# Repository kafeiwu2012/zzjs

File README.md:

# RoomGuard：楼宇房间环境监测与异常声光告警系统

面向中职双人参赛项目的完整资料库：**系统工程、Arduino 固件、树莓派部署、教师教学、学生岗位学习手册及比赛展示资料**。

当前推荐 **V2**。实物基线为 **101＝ESP32、102＝ESP8266、树莓派 3B、MW305R 路由器**；同协议节点可经手机配网和管理者批准扩展。温湿度仅展示，烟雾或火焰触发对应房间本地声光。

## 先下载这三个包

| 资料包 | 用途 | 下载 |
| --- | --- | --- |
| 系统完整交付包 | 源码、固件、APK／EXE、手册、架构、PPT、测试证据 | [下载 V2 完整包](downloads/v2/RoomGuard_V2_完整交付包.zip?raw=1) |
| 教师教学资料包 | 36 学时、12 任务的项目化教学、任务单、评价与参考答案 | [下载教师教学包](downloads/v2/RoomGuard_V2_中职竞赛教学资料包.zip?raw=1) |
| 学生双岗位手册包 | A 系统操作、B 展示演讲及双人配合卡，提供 Word／PDF | [下载学生学习包](downloads/v2/RoomGuard_V2_参赛学生双岗位学习手册.zip?raw=1) |

文件已保存在本 GitHub 仓库，可在此下载，无需依赖原 Codex 会话下载链接。也可点击 **Code → Download ZIP** 获取整个资料库，或使用 `git clone https://github.com/kafeiwu2012/zzjs.git`。

## 按角色开始

- **辅导教师**：[教学指导手册 PDF](teaching/standalone/教师项目化教学指导手册_V2.pdf) · [可编辑 Word](teaching/standalone/教师项目化教学指导手册_V2.docx?raw=1) · [教师后台手册](manuals/教师后台操作手册_V2.pdf)。
- **学生 A／系统操作**：[学习手册 PDF](students/standalone/参赛学生A_系统操作学习手册_V2.pdf) · [可编辑 Word](students/standalone/参赛学生A_系统操作学习手册_V2.docx?raw=1)。
- **学生 B／展示演讲**：[学习手册 PDF](students/standalone/参赛学生B_展示演讲学习手册_V2.pdf) · [可编辑 Word](students/standalone/参赛学生B_展示演讲学习手册_V2.docx?raw=1)。
- **两人协作**：[比赛配合随身卡](students/standalone/双人比赛配合随身卡_V2.pdf) · [比赛 PPT](presentation/RoomGuard_V2_竞赛展示_教师后台与自适应节点.pptx?raw=1) · [PPT 预览 PDF](presentation/RoomGuard_V2_竞赛展示_教师后台与自适应节点.pdf)。
- **安装与开发**：[树莓派新手手册](manuals/树莓派新手部署与维护_V2.pdf) · [Arduino 与手机配网](manuals/ESP手机配网与Arduino烧录_V2.pdf) · [开发与重建](manuals/开发与重建指南_V2.pdf) · [可浏览源码](system/roomguard-v2/README.md)。

## 资料怎样组织

| 目录 | 内容 |
| --- | --- |
| [`system/roomguard-v2/`](system/roomguard-v2/) | V2 完整可浏览工程：服务、Arduino、客户端、部署、硬件草案、测试和文档 |
| [`manuals/`](manuals/) | 单独查阅／下载的系统需求、部署、维护、验收等 V2 文档 |
| [`teaching/`](teaching/) | 教师教学资料、学生任务单、评价与编辑源稿 |
| [`students/`](students/) | 两名学生各自的学习手册、配合卡及源稿 |
| [`presentation/`](presentation/) | V2 比赛 PPT、PDF 和页面总览 |
| [`downloads/v2/`](downloads/v2/) | V2 原交付压缩包、Arduino 包、基板参考包、APK 与 EXE |
| [`archive/`](archive/) | V1.0、V1.1 和早期汇总资料，保留历史参考 |
| [`docs/资料总目录.md`](docs/资料总目录.md) | 原有 93 份交付文件在仓库中的逐项位置 |
| [`CHECKSUMS.sha256`](CHECKSUMS.sha256) | 本仓库全部资料的 SHA256 校验清单 |

## 运行入口

开发先进入 `system/roomguard-v2/`。Pi 首次安装按新手手册执行 `sudo bash deploy/install.sh`；已有部署先备份，再使用升级流程。首次新装节点清单为空，配网并经教师批准后才出现房间。

- 工作台：`http://实际树莓派IP:8080/`
- 只读大屏：`http://实际树莓派IP:8080/?screen=1`
- 教师后台：`http://实际树莓派IP:8080/teacher`
- Arduino：`arduino/RoomGuard_ESP32/RoomGuard_ESP32.ino` 与 `arduino/RoomGuard_ESP8266/RoomGuard_ESP8266.ino`

两种芯片共用业务逻辑，**不能互刷同一个 BIN**。Windows EXE 使用系统 Edge；Android APK 面向 API22／Android5.1，后台行为须在指定手机实测。

## 验证范围与版本说明

已交付记录包含两平台 Arduino 编译、21 项自动测试、本地告警状态机、MQTT 集成及浏览器检查。它们不代替目标 Pi、ESP 电平与传感器、手机 AP、Windows 和 OPPO 锁屏的实物验收，详见[测试说明](manuals/测试与交付说明_V2.pdf)。本系统为教学演示原型。

基板仍为 **未布线审阅草案**，排距、模块尺寸／脚序等待核验，不能直接下单制造。网络恢复上报当前状态，不保证补齐完整离线历史。新 APK 开发签名与早期版本不同，必要时先卸载旧版。

公开上传排除了私钥、运行账号配置、数据库和缓存。早期三个归档 ZIP 中的上游 SSL 示例私钥已递归清理；旧校验记录仅作追溯，现上传字节以本仓库 `CHECKSUMS.sha256` 为准。可浏览 Pi 手册已校正为“首次创建服务器 MQTT 账号，节点凭据在批准时发放”。详见[上传与校验说明](docs/上传与校验说明.md)。

第三方库保留上游许可，见 [THIRD_PARTY.md](THIRD_PARTY.md) 和工程库目录。仓库没有另行替上游组件授予统一许可证。

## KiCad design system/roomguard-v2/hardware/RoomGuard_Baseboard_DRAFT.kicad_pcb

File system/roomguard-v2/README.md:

# RoomGuard V2.0 · 自适应节点与教师管理中心

这是新的主交付版本，保留V1.1硬件参考，但网络配置与节点管理以V2文档为准。

## 阅读顺序

1. docs/需求与协议基线_V2.md：范围、协议、接入与权限。
2. docs/树莓派新手部署与维护_V2.md：写卡、SSH、安装、升级、诊断与恢复。
3. docs/ESP手机配网与Arduino烧录_V2.md：同型号通用固件，手机连接加密热点配网。
4. docs/教师后台操作手册_V2.md：批准设备、分配学生权限、节点参数、服务与终端显示。
5. docs/测试与交付说明_V2.md：软件验证与实物待验收项。
6. docs/开发与重建指南_V2.md：源码入口、电脑演示、软件回归和各平台重建。
7. docs/双人演讲与教师排练_V2.md：双人展示、逐页讲稿与答辩。

首次安装：sudo bash deploy/install.sh；已有V1.1升级：先备份，再sudo bash deploy/update.sh。不把生产环境设置为DEMO或TEST_HELPER。

监控工作台：http://树莓派IP:8080/；教师后台：http://树莓派IP:8080/teacher。首次账号admin，密码安装时设置。新安装节点清单为空；生成接入码、手机配网、教师批准后自动出现。

Arduino工程：arduino/RoomGuard_ESP32与arduino/RoomGuard_ESP8266。固定版本库在arduino/libraries。无编译内置的SSID、房间或共享MQTT密码，两种芯片分别编译；第一次仍用USB烧录，不提供OTA。node_options.h是硬件参数，先核对实际接线。

只看模拟演示：安装server/requirements.txt后，在根目录python -m tools.run_demo，打开http://127.0.0.1:8080。模拟账号admin／DemoOnly-123456，三模拟节点；DEMO不修改真实服务或账号，不用于证明实物通过。

EXE需要Windows10 x64和Edge；APK minSdk22，开发测试签名，旧版可能需卸载再安装。后台告警仍需手机网络与系统许可及指定OPPO真机验收。

hardware是V1.1基板审阅草案，不是制造版；机械尺寸待核验，PCB未布线。旧版资料仅作历史参考，不把旧secrets.h配置流程用于V2新工程。

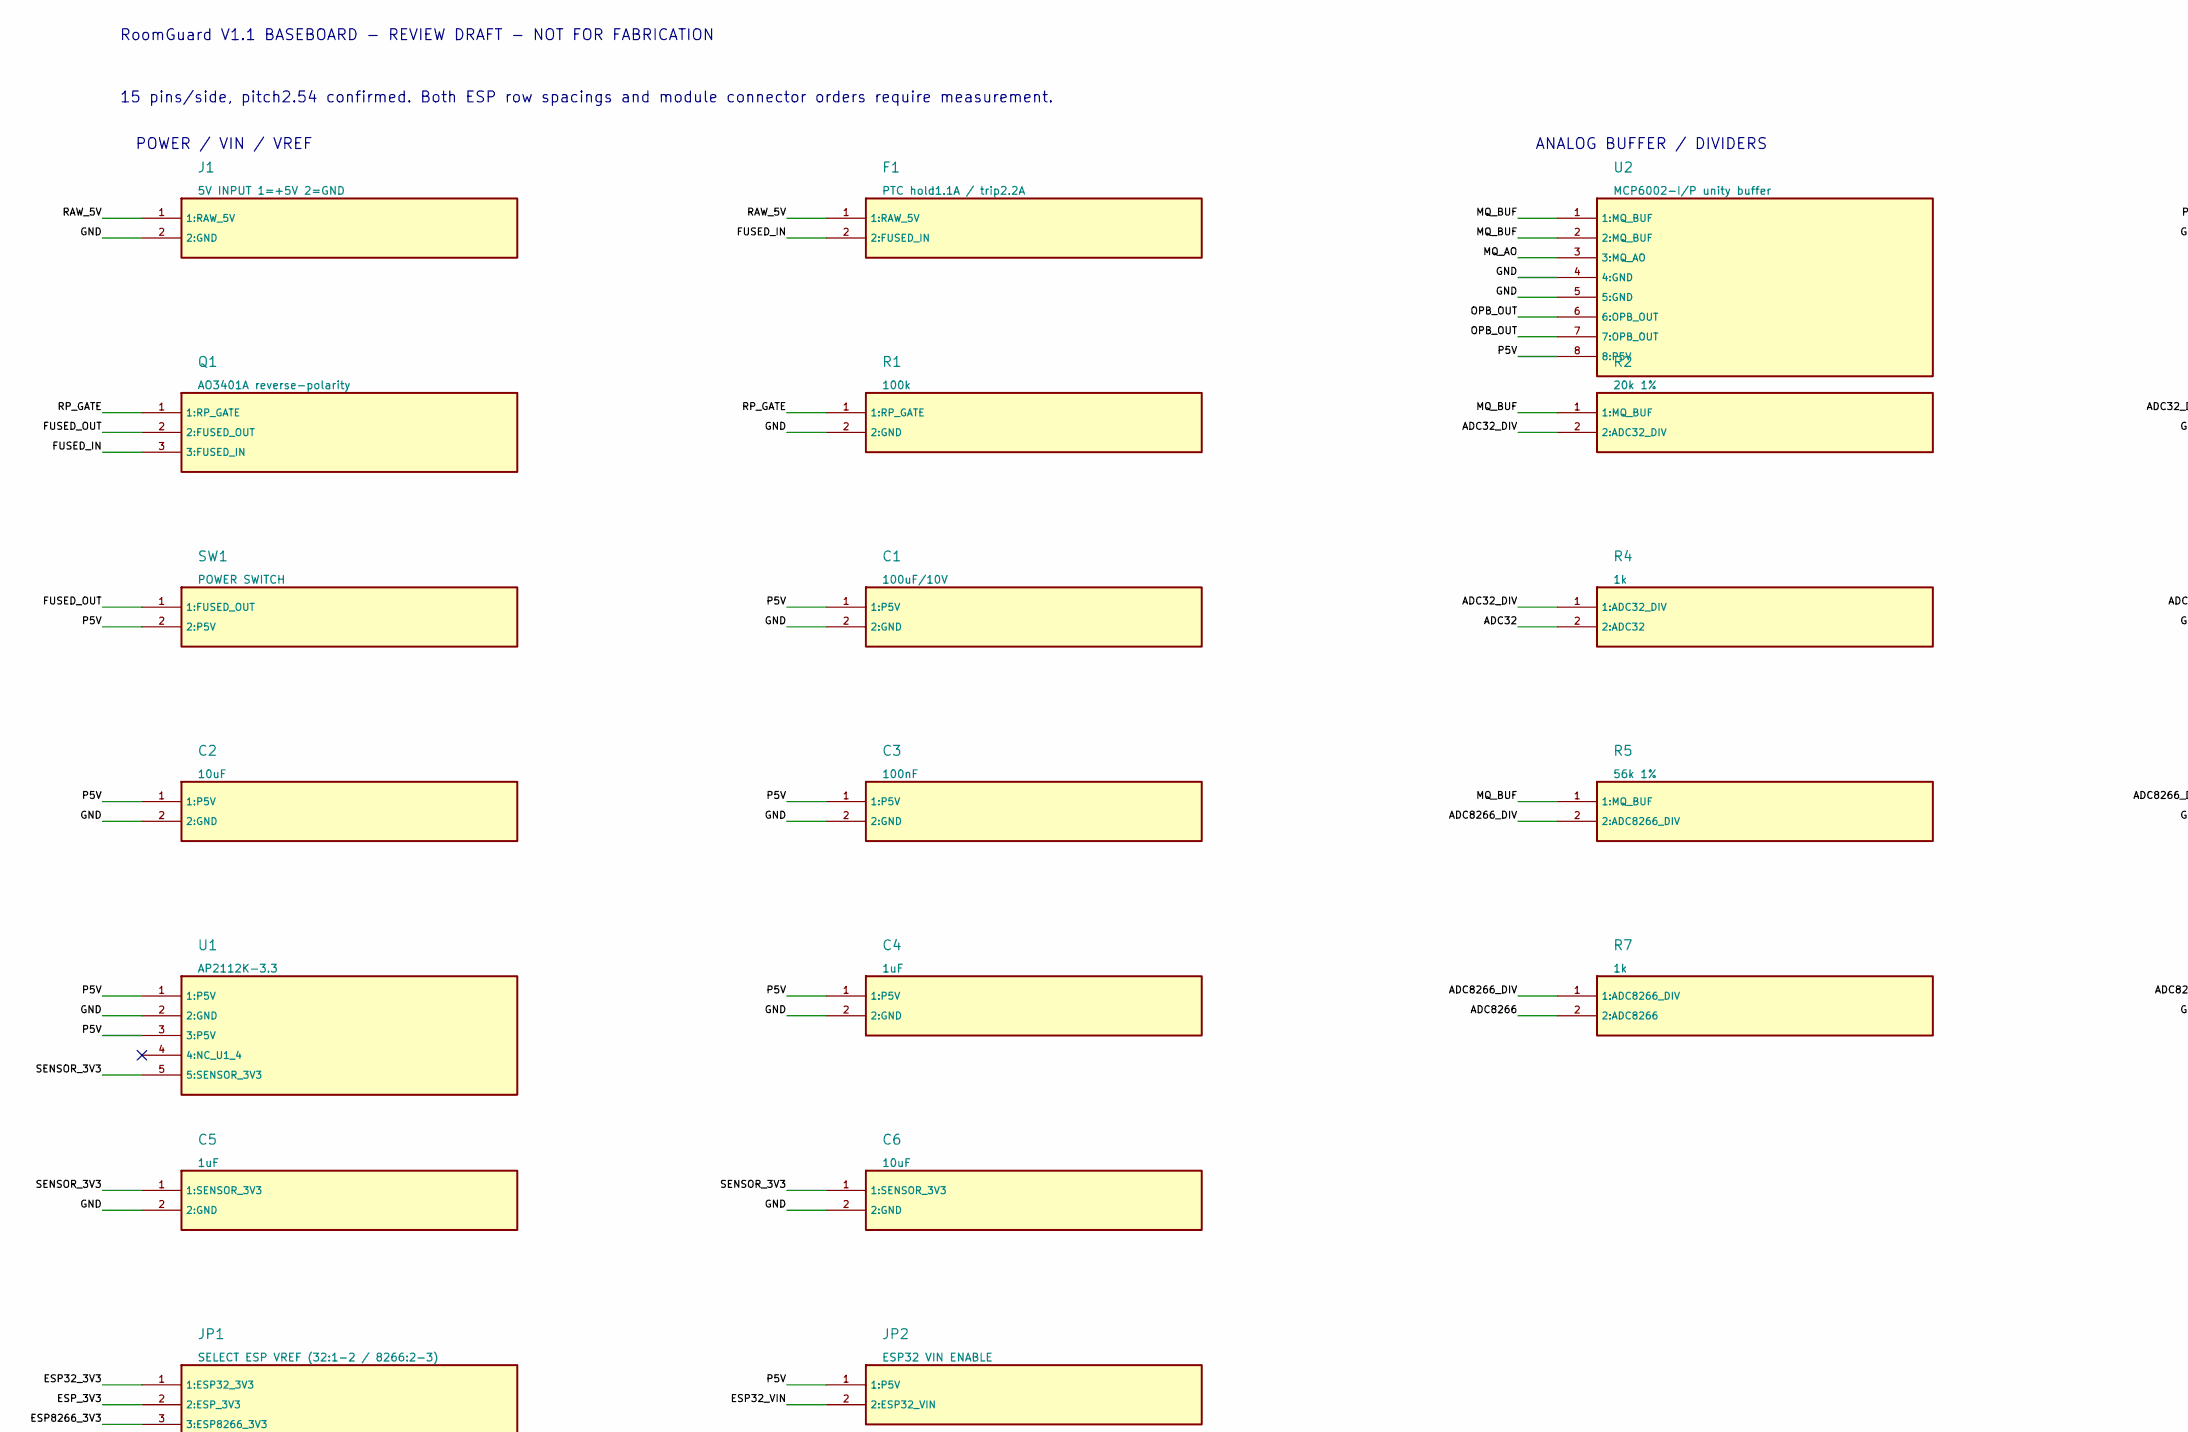
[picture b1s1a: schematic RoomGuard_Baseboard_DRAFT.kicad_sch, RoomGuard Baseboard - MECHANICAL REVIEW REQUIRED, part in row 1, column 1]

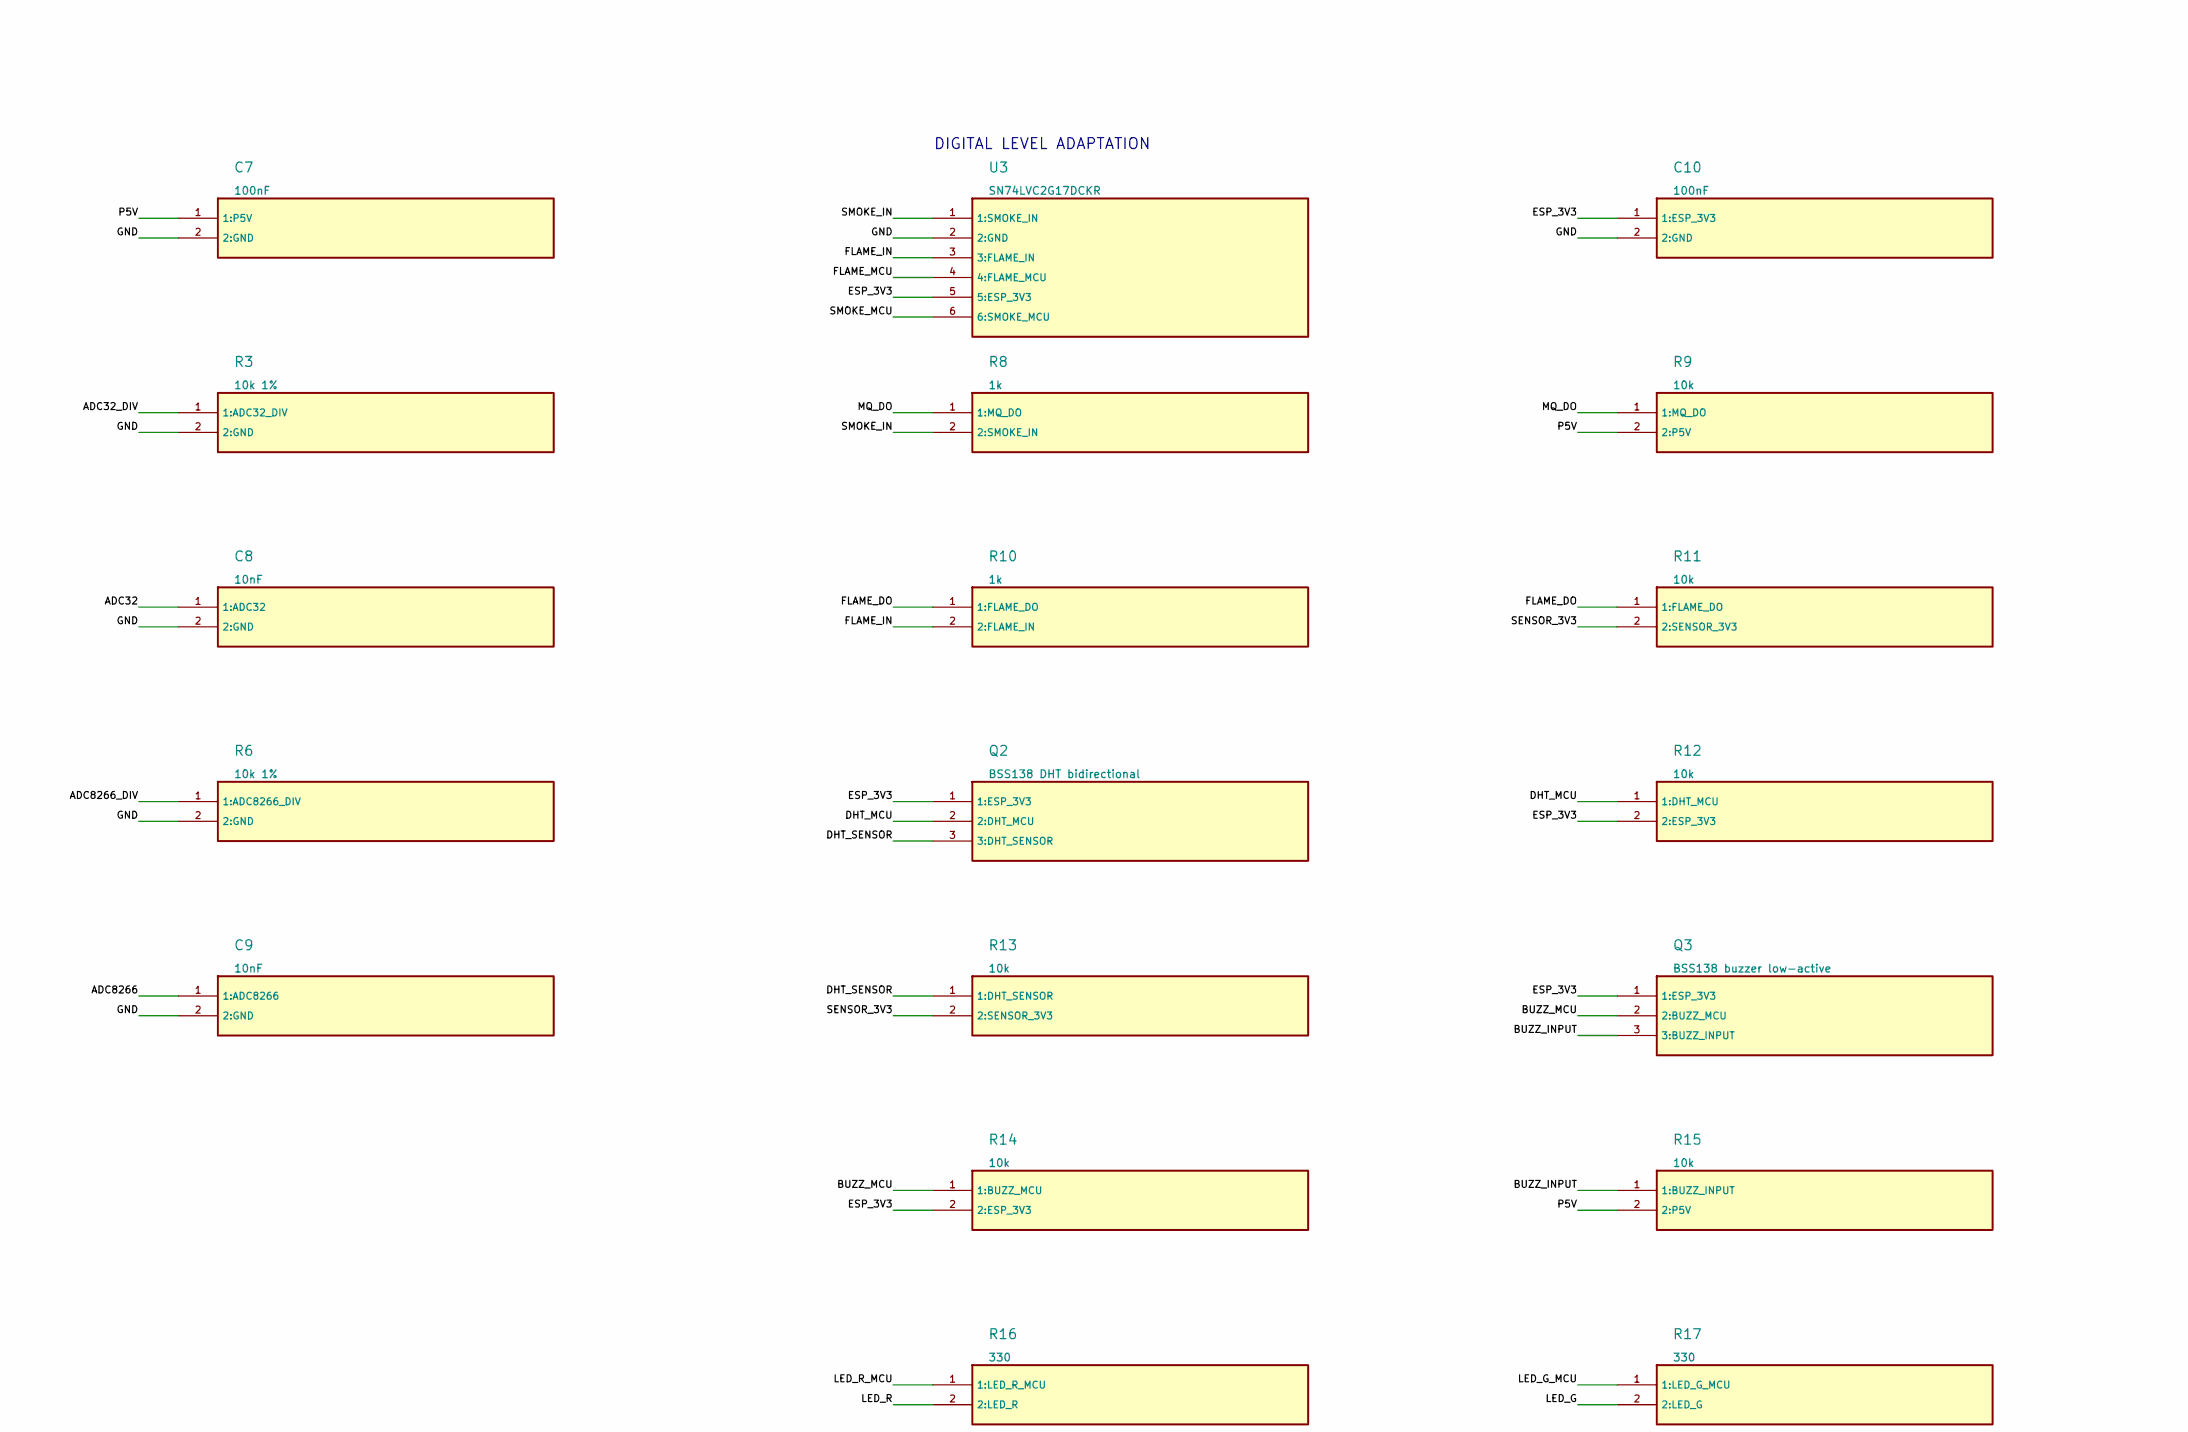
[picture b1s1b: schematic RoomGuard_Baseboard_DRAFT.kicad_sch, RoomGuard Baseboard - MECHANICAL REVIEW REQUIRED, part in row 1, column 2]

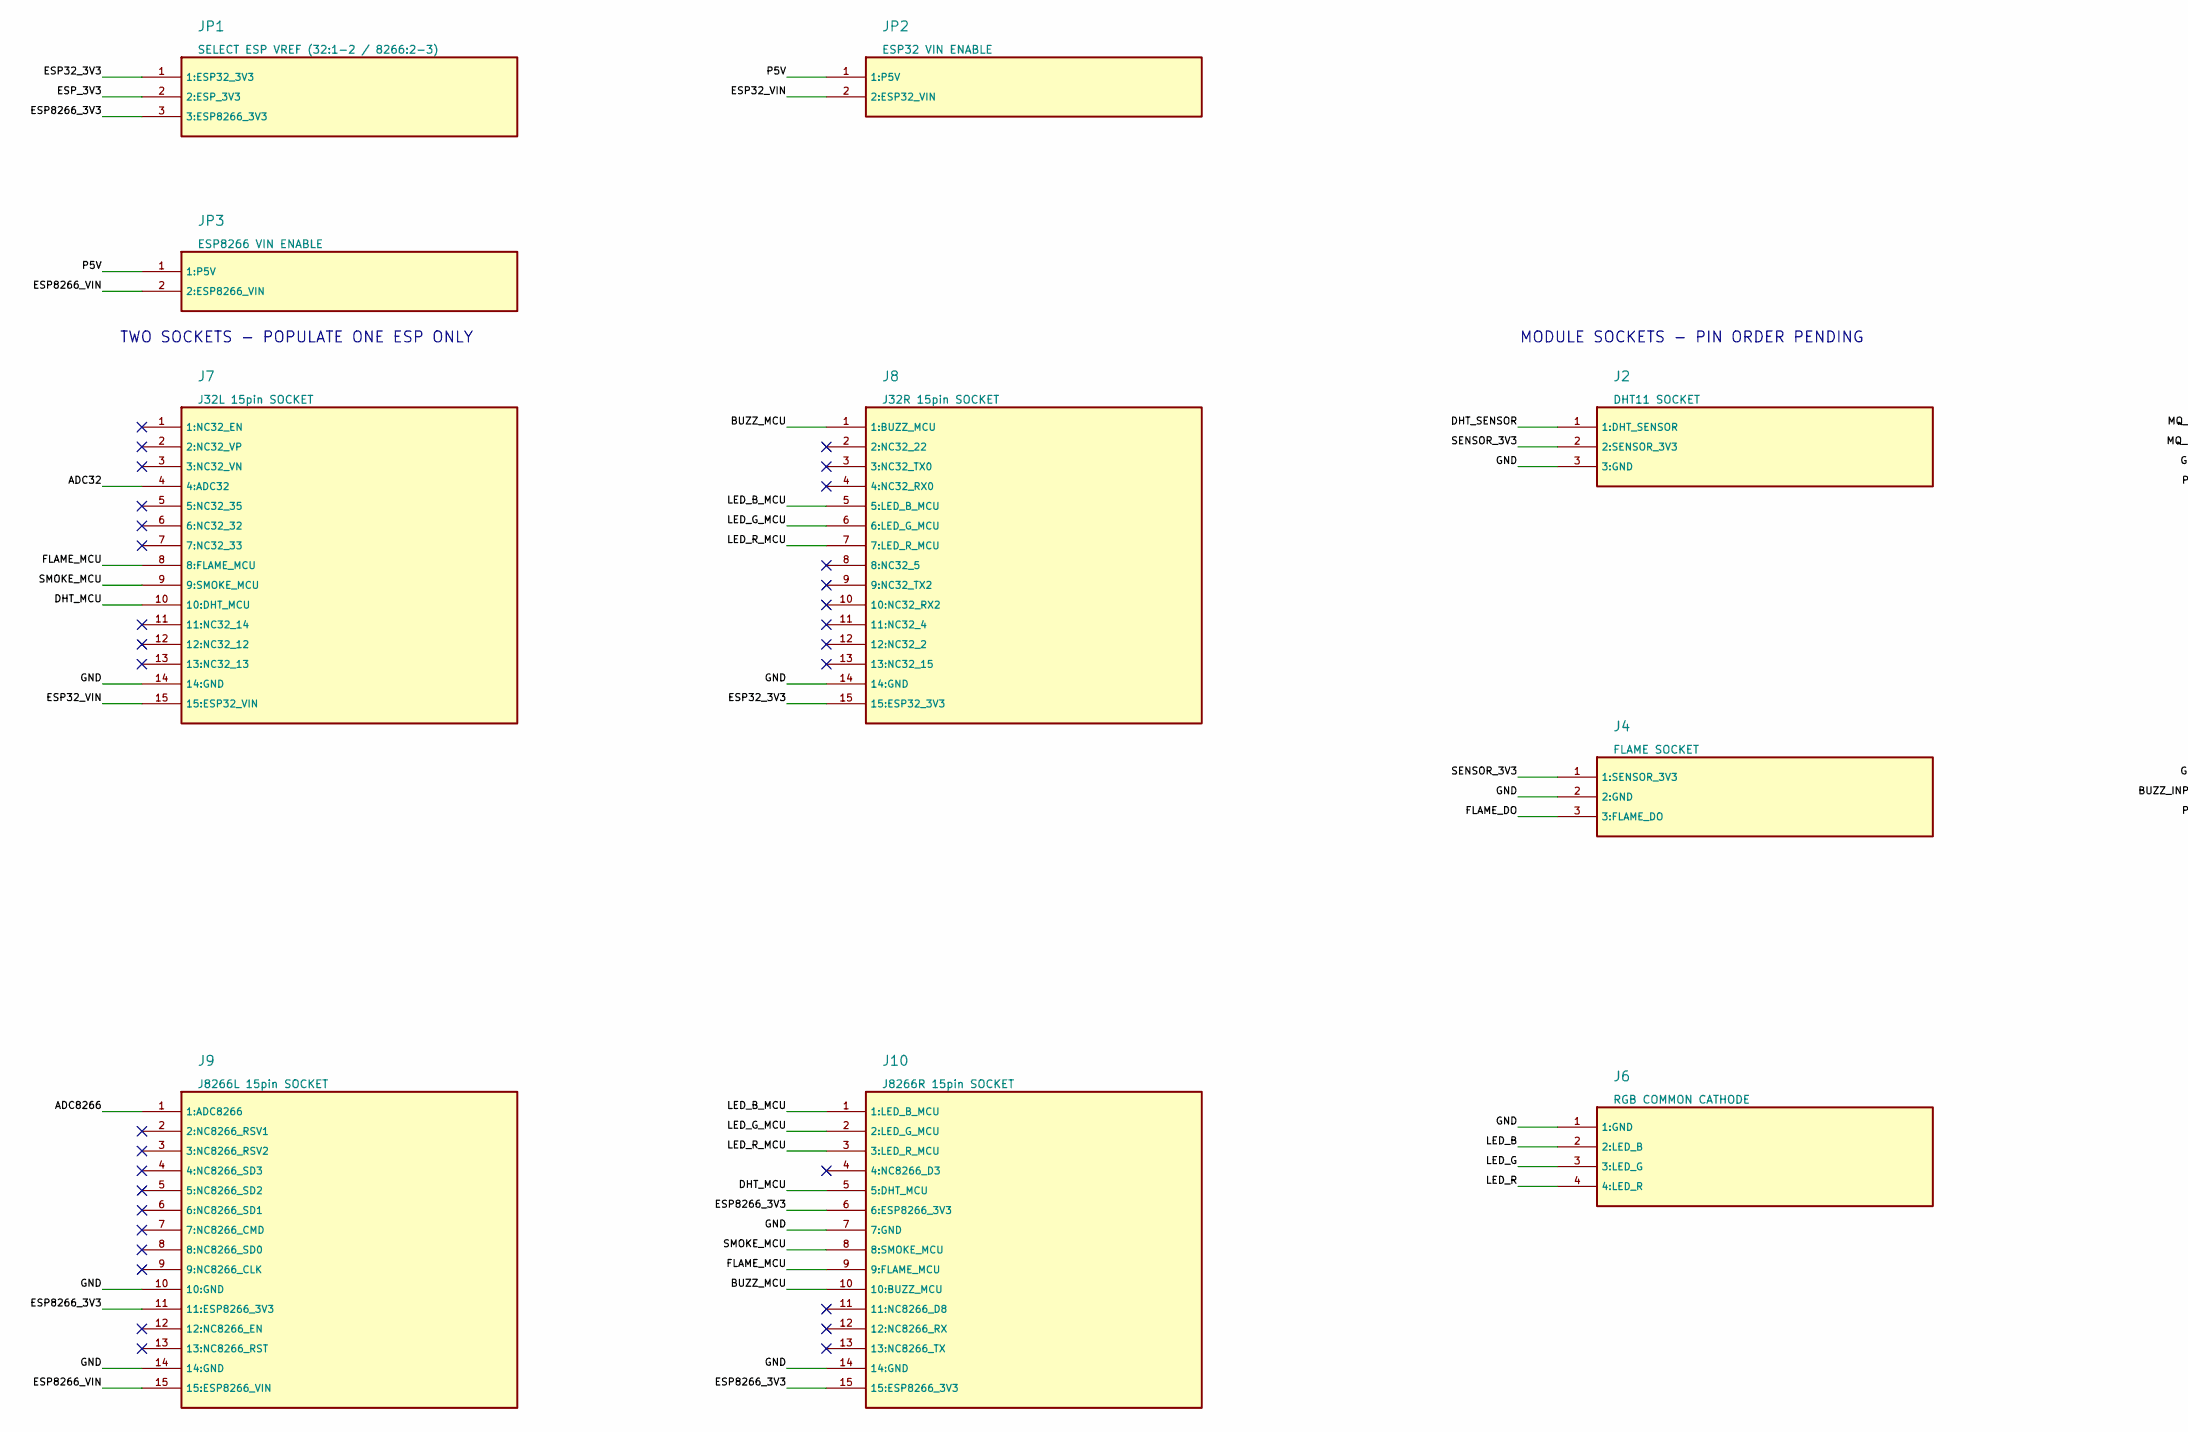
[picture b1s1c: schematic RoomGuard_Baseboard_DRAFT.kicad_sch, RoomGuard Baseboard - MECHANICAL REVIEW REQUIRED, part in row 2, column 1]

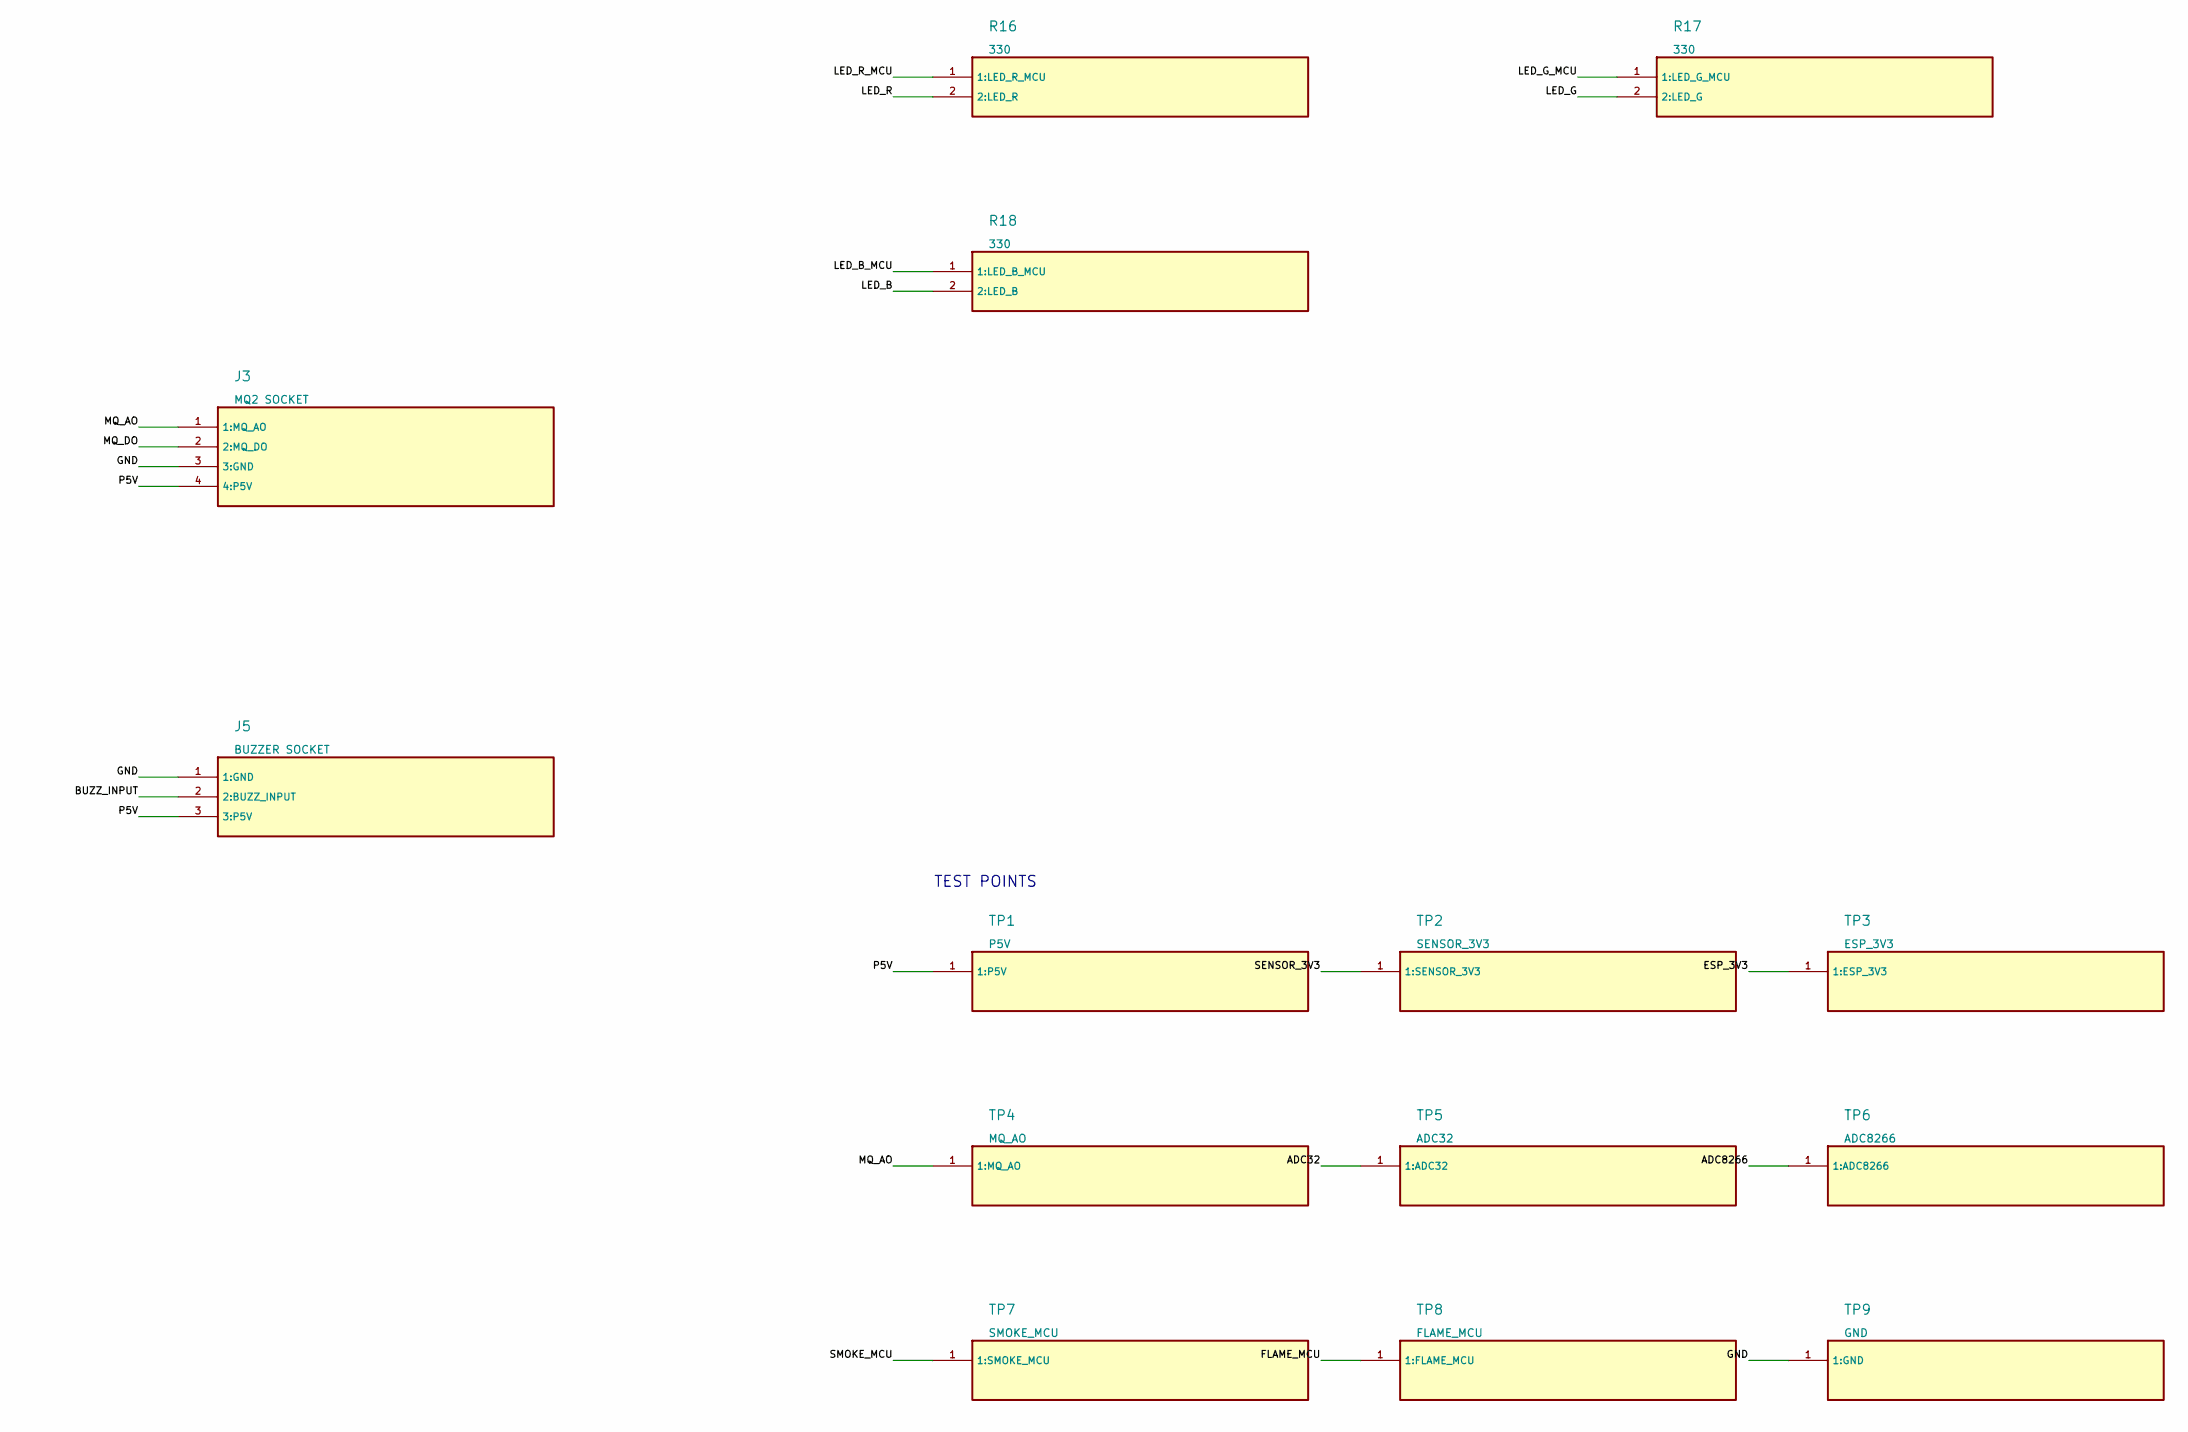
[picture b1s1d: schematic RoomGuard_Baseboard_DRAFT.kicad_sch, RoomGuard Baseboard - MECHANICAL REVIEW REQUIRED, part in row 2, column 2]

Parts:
C1: 100uF/10V; C_0805_2012Metric
C2, C6: 10uF; C_0805_2012Metric
C3, C7, C10: 100nF; C_0805_2012Metric
C4, C5: 1uF; C_0805_2012Metric
C8, C9: 10nF; C_0805_2012Metric
F1: PTC hold1.1A / trip2.2A; Fuse_1206_3216Metric
J1: 5V INPUT 1=+5V 2=GND; TerminalBlock_bornier-2_P5.08mm
J2: DHT11 SOCKET; PinSocket_1x03_P2.54mm_Vertical
J3: MQ2 SOCKET; PinSocket_1x04_P2.54mm_Vertical
J4: FLAME SOCKET; PinSocket_1x03_P2.54mm_Vertical
J5: BUZZER SOCKET; PinSocket_1x03_P2.54mm_Vertical
J6: RGB COMMON CATHODE; PinSocket_1x04_P2.54mm_Vertical
J7: J32L 15pin SOCKET; PinSocket_1x15_P2.54mm_Vertical
J8: J32R 15pin SOCKET; PinSocket_1x15_P2.54mm_Vertical
J9: J8266L 15pin SOCKET; PinSocket_1x15_P2.54mm_Vertical
J10: J8266R 15pin SOCKET; PinSocket_1x15_P2.54mm_Vertical
JP1: SELECT ESP VREF (32:1-2 / 8266:2-3); PinHeader_1x03_P2.54mm_Vertical
JP2: ESP32 VIN ENABLE; PinHeader_1x02_P2.54mm_Vertical
JP3: ESP8266 VIN ENABLE; PinHeader_1x02_P2.54mm_Vertical
Q1: AO3401A reverse-polarity; SOT-23
Q2: BSS138 DHT bidirectional; SOT-23
Q3: BSS138 buzzer low-active; SOT-23
R1: 100k; R_0805_2012Metric
R2: 20k 1%; R_0805_2012Metric
R3, R6: 10k 1%; R_0805_2012Metric
R4, R7, R8, R10: 1k; R_0805_2012Metric
R5: 56k 1%; R_0805_2012Metric
R9, R11, R12, R13, R14, R15: 10k; R_0805_2012Metric
R16, R17, R18: 330; R_0805_2012Metric
SW1: POWER SWITCH; PinHeader_1x02_P2.54mm_Vertical
TP1: P5V; TestPoint_Pad_D2.0mm
TP2: SENSOR_3V3; TestPoint_Pad_D2.0mm
TP3: ESP_3V3; TestPoint_Pad_D2.0mm
TP4: MQ_AO; TestPoint_Pad_D2.0mm
TP5: ADC32; TestPoint_Pad_D2.0mm
TP6: ADC8266; TestPoint_Pad_D2.0mm
TP7: SMOKE_MCU; TestPoint_Pad_D2.0mm
TP8: FLAME_MCU; TestPoint_Pad_D2.0mm
TP9: GND; TestPoint_Pad_D2.0mm
U1: AP2112K-3.3; SOT-23-5
U2: MCP6002-I/P unity buffer; DIP-8_W7.62mm
U3: SN74LVC2G17DCKR; SOT-363_SC-70-6

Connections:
ADC32: C8.1 (1:ADC32), J7.4 (4:ADC32), R4.2 (2:ADC32), TP5.1
ADC32_DIV: R2.2 (2:ADC32_DIV), R3.1 (1:ADC32_DIV), R4.1 (1:ADC32_DIV)
ADC8266: C9.1 (1:ADC8266), J9.1 (1:ADC8266), R7.2 (2:ADC8266), TP6.1
ADC8266_DIV: R5.2 (2:ADC8266_DIV), R6.1 (1:ADC8266_DIV), R7.1 (1:ADC8266_DIV)
BUZZ_INPUT: J5.2 (2:BUZZ_INPUT), Q3.3 (3:BUZZ_INPUT), R15.1 (1:BUZZ_INPUT)
BUZZ_MCU: J8.1 (1:BUZZ_MCU), J10.10 (10:BUZZ_MCU), Q3.2 (2:BUZZ_MCU), R14.1 (1:BUZZ_MCU)
DHT_MCU: J7.10 (10:DHT_MCU), J10.5 (5:DHT_MCU), Q2.2 (2:DHT_MCU), R12.1 (1:DHT_MCU)
DHT_SENSOR: J2.1 (1:DHT_SENSOR), Q2.3 (3:DHT_SENSOR), R13.1 (1:DHT_SENSOR)
ESP32_3V3: J8.15 (15:ESP32_3V3), JP1.1 (1:ESP32_3V3)
ESP32_VIN: J7.15 (15:ESP32_VIN), JP2.2 (2:ESP32_VIN)
ESP8266_3V3: J9.11 (11:ESP8266_3V3), J10.6 (6:ESP8266_3V3), J10.15 (15:ESP8266_3V3), JP1.3 (3:ESP8266_3V3)
ESP8266_VIN: J9.15 (15:ESP8266_VIN), JP3.2 (2:ESP8266_VIN)
ESP_3V3: C10.1 (1:ESP_3V3), JP1.2 (2:ESP_3V3), Q2.1 (1:ESP_3V3), Q3.1 (1:ESP_3V3), R12.2 (2:ESP_3V3), R14.2 (2:ESP_3V3), TP3.1, U3.5 (5:ESP_3V3)
FLAME_DO: J4.3 (3:FLAME_DO), R10.1 (1:FLAME_DO), R11.1 (1:FLAME_DO)
FLAME_IN: R10.2 (2:FLAME_IN), U3.3 (3:FLAME_IN)
FLAME_MCU: J7.8 (8:FLAME_MCU), J10.9 (9:FLAME_MCU), TP8.1, U3.4 (4:FLAME_MCU)
FUSED_IN: F1.2 (2:FUSED_IN), Q1.3 (3:FUSED_IN)
FUSED_OUT: Q1.2 (2:FUSED_OUT), SW1.1 (1:FUSED_OUT)
GND: C1.2 (2:GND), C2.2 (2:GND), C3.2 (2:GND), C4.2 (2:GND), C5.2 (2:GND), C6.2 (2:GND), C7.2 (2:GND), C8.2 (2:GND), C9.2 (2:GND), C10.2 (2:GND), J1.2 (2:GND), J2.3 (3:GND), J3.3 (3:GND), J4.2 (2:GND), J5.1 (1:GND), J6.1 (1:GND), J7.14 (14:GND), J8.14 (14:GND), J9.10 (10:GND), J9.14 (14:GND), J10.7 (7:GND), J10.14 (14:GND), R1.2 (2:GND), R3.2 (2:GND), R6.2 (2:GND), TP9.1, U1.2 (2:GND), U2.4 (4:GND), U2.5 (5:GND), U3.2 (2:GND)
LED_B: J6.2 (2:LED_B), R18.2 (2:LED_B)
LED_B_MCU: J8.5 (5:LED_B_MCU), J10.1 (1:LED_B_MCU), R18.1 (1:LED_B_MCU)
LED_G: J6.3 (3:LED_G), R17.2 (2:LED_G)
LED_G_MCU: J8.6 (6:LED_G_MCU), J10.2 (2:LED_G_MCU), R17.1 (1:LED_G_MCU)
LED_R: J6.4 (4:LED_R), R16.2 (2:LED_R)
LED_R_MCU: J8.7 (7:LED_R_MCU), J10.3 (3:LED_R_MCU), R16.1 (1:LED_R_MCU)
MQ_AO: J3.1 (1:MQ_AO), TP4.1, U2.3 (3:MQ_AO)
MQ_BUF: R2.1 (1:MQ_BUF), R5.1 (1:MQ_BUF), U2.1 (1:MQ_BUF), U2.2 (2:MQ_BUF)
MQ_DO: J3.2 (2:MQ_DO), R8.1 (1:MQ_DO), R9.1 (1:MQ_DO)
OPB_OUT: U2.6 (6:OPB_OUT), U2.7 (7:OPB_OUT)
P5V: C1.1 (1:P5V), C2.1 (1:P5V), C3.1 (1:P5V), C4.1 (1:P5V), C7.1 (1:P5V), J3.4 (4:P5V), J5.3 (3:P5V), JP2.1 (1:P5V), JP3.1 (1:P5V), R9.2 (2:P5V), R15.2 (2:P5V), SW1.2 (2:P5V), TP1.1, U1.1 (1:P5V), U1.3 (3:P5V), U2.8 (8:P5V)
RAW_5V: F1.1 (1:RAW_5V), J1.1 (1:RAW_5V)
RP_GATE: Q1.1 (1:RP_GATE), R1.1 (1:RP_GATE)
SENSOR_3V3: C5.1 (1:SENSOR_3V3), C6.1 (1:SENSOR_3V3), J2.2 (2:SENSOR_3V3), J4.1 (1:SENSOR_3V3), R11.2 (2:SENSOR_3V3), R13.2 (2:SENSOR_3V3), TP2.1, U1.5 (5:SENSOR_3V3)
SMOKE_IN: R8.2 (2:SMOKE_IN), U3.1 (1:SMOKE_IN)
SMOKE_MCU: J7.9 (9:SMOKE_MCU), J10.8 (8:SMOKE_MCU), TP7.1, U3.6 (6:SMOKE_MCU)

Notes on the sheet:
RoomGuard V1.1 BASEBOARD - REVIEW DRAFT - NOT FOR FABRICATION
15 pins/side, pitch2.54 confirmed. Both ESP row spacings and module connector orders require measurement.
POWER / VIN / VREF
ANALOG BUFFER / DIVIDERS
DIGITAL LEVEL ADAPTATION
TWO SOCKETS - POPULATE ONE ESP ONLY
MODULE SOCKETS - PIN ORDER PENDING
TEST POINTS

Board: 2 copper layers, 58 parts (0 on the bottom side), 35 nets, no tracks yet.

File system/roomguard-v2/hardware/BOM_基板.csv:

位号,器件或参数,数量,封装,功能分区,核验说明
J1,5V INPUT 1=+5V 2=GND,1,TerminalBlock:TerminalBlock_bornier-2_P5.08mm,power,Regulated5V only; no12V
F1,PTC hold1.1A / trip2.2A,1,Fuse:Fuse_1206_3216Metric,power,Verify peak current and thermal derating
Q1,AO3401A reverse-polarity,1,Package_TO_SOT_SMD:SOT-23,power,Pin1G 2S 3D; verify exact part
R1,100k,1,Resistor_SMD:R_0805_2012Metric,power,
SW1,POWER SWITCH,1,Connector_PinHeader_2.54mm:PinHeader_1x02_P2.54mm_Vertical,power,External switch header; do not bridge with metal while powered
C1,100uF/10V,1,Capacitor_SMD:C_0805_2012Metric,power,
C2,10uF,1,Capacitor_SMD:C_0805_2012Metric,power,
C3,100nF,1,Capacitor_SMD:C_0805_2012Metric,power,
U1,AP2112K-3.3,1,Package_TO_SOT_SMD:SOT-23-5,power,600mA maximum datasheet rating; design sensor load<=100mA pending measurement
C4,1uF,1,Capacitor_SMD:C_0805_2012Metric,power,
C5,1uF,1,Capacitor_SMD:C_0805_2012Metric,power,
C6,10uF,1,Capacitor_SMD:C_0805_2012Metric,power,
JP1,SELECT ESP VREF (32:1-2 / 8266:2-3),1,Connector_PinHeader_2.54mm:PinHeader_1x03_P2.54mm_Vertical,power,One shunt only. Never bridge external LDO to ESP3V3
JP2,ESP32 VIN ENABLE,1,Connector_PinHeader_2.54mm:PinHeader_1x02_P2.54mm_Vertical,power,Install only for selected board
JP3,ESP8266 VIN ENABLE,1,Connector_PinHeader_2.54mm:PinHeader_1x02_P2.54mm_Vertical,power,Install only for selected board
U2,MCP6002-I/P unity buffer,1,Package_DIP:DIP-8_W7.62mm,analog,"Unused amplifier B is a ground follower, not floating"
C7,100nF,1,Capacitor_SMD:C_0805_2012Metric,analog,
R2,20k 1%,1,Resistor_SMD:R_0805_2012Metric,analog,
R3,10k 1%,1,Resistor_SMD:R_0805_2012Metric,analog,
R4,1k,1,Resistor_SMD:R_0805_2012Metric,analog,
C8,10nF,1,Capacitor_SMD:C_0805_2012Metric,analog,
R5,56k 1%,1,Resistor_SMD:R_0805_2012Metric,analog,
R6,10k 1%,1,Resistor_SMD:R_0805_2012Metric,analog,
R7,1k,1,Resistor_SMD:R_0805_2012Metric,analog,
C9,10nF,1,Capacitor_SMD:C_0805_2012Metric,analog,
U3,SN74LVC2G17DCKR,1,Package_TO_SOT_SMD:SOT-363_SC-70-6,logic,5.5V tolerant inputs and Ioff; do not replace with non5V-tolerant HC buffer
C10,100nF,1,Capacitor_SMD:C_0805_2012Metric,logic,
R8,1k,1,Resistor_SMD:R_0805_2012Metric,logic,
R9,10k,1,Resistor_SMD:R_0805_2012Metric,logic,
R10,1k,1,Resistor_SMD:R_0805_2012Metric,logic,
R11,10k,1,Resistor_SMD:R_0805_2012Metric,logic,
Q2,BSS138 DHT bidirectional,1,Package_TO_SOT_SMD:SOT-23,logic,Gate ESP VREF; source MCU; drain sensor. No inversion
R12,10k,1,Resistor_SMD:R_0805_2012Metric,logic,
R13,10k,1,Resistor_SMD:R_0805_2012Metric,logic,
Q3,BSS138 buzzer low-active,1,Package_TO_SOT_SMD:SOT-23,logic,"Module input load must be verified; MCU HIGH=off, LOW=on"
R14,10k,1,Resistor_SMD:R_0805_2012Metric,logic,
R15,10k,1,Resistor_SMD:R_0805_2012Metric,logic,
R16,330,1,Resistor_SMD:R_0805_2012Metric,logic,
R17,330,1,Resistor_SMD:R_0805_2012Metric,logic,
R18,330,1,Resistor_SMD:R_0805_2012Metric,logic,
J2,DHT11 SOCKET,1,Connector_PinSocket_2.54mm:PinSocket_1x03_P2.54mm_Vertical,modules,J_DHT; Reference order DATA VCC GND; physical dimensions pending
J3,MQ2 SOCKET,1,Connector_PinSocket_2.54mm:PinSocket_1x04_P2.54mm_Vertical,modules,J_MQ; Reference order AO DO GND VCC; verify actual module
J4,FLAME SOCKET,1,Connector_PinSocket_2.54mm:PinSocket_1x03_P2.54mm_Vertical,modules,J_FLAME; Reference order VCC GND DO; verify actual module
J5,BUZZER SOCKET,1,Connector_PinSocket_2.54mm:PinSocket_1x03_P2.54mm_Vertical,modules,J_BUZZ; Reference order GND IO VCC; verify actual module
J6,RGB COMMON CATHODE,1,Connector_PinSocket_2.54mm:PinSocket_1x04_P2.54mm_Vertical,modules,J_RGB; Reference order GND B G R; verify actual module
J7,J32L 15pin SOCKET,1,Connector_PinSocket_2.54mm:PinSocket_1x15_P2.54mm_Vertical,sockets,J32L; Pitch2.54mm confirmed; row spacing UNKNOWN; pin labels must be checked against actual board
J8,J32R 15pin SOCKET,1,Connector_PinSocket_2.54mm:PinSocket_1x15_P2.54mm_Vertical,sockets,J32R; Pitch2.54mm confirmed; row spacing UNKNOWN; pin labels must be checked against actual board
J9,J8266L 15pin SOCKET,1,Connector_PinSocket_2.54mm:PinSocket_1x15_P2.54mm_Vertical,sockets,J8266L; Pitch2.54mm confirmed; row spacing UNKNOWN; pin labels must be checked against actual board
J10,J8266R 15pin SOCKET,1,Connector_PinSocket_2.54mm:PinSocket_1x15_P2.54mm_Vertical,sockets,J8266R; Pitch2.54mm confirmed; row spacing UNKNOWN; pin labels must be checked against actual board
TP1,P5V,1,TestPoint:TestPoint_Pad_D2.0mm,testpoints,
TP2,SENSOR_3V3,1,TestPoint:TestPoint_Pad_D2.0mm,testpoints,
TP3,ESP_3V3,1,TestPoint:TestPoint_Pad_D2.0mm,testpoints,
TP4,MQ_AO,1,TestPoint:TestPoint_Pad_D2.0mm,testpoints,
TP5,ADC32,1,TestPoint:TestPoint_Pad_D2.0mm,testpoints,
TP6,ADC8266,1,TestPoint:TestPoint_Pad_D2.0mm,testpoints,
TP7,SMOKE_MCU,1,TestPoint:TestPoint_Pad_D2.0mm,testpoints,
TP8,FLAME_MCU,1,TestPoint:TestPoint_Pad_D2.0mm,testpoints,
TP9,GND,1,TestPoint:TestPoint_Pad_D2.0mm,testpoints,

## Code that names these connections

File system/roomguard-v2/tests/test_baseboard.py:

from pathlib import Path
import json,re
H=Path(__file__).resolve().parents[1]/'hardware'
def sexp(text):
 tokens=re.findall(r'\(|\)|"(?:\\.|[^"\\])*"|[^\s()]+',text);it=iter(tokens)
 def read(t):
  if t=='(':
   a=[]
   for t in it:
    if t==')':return a
    a.append(read(t))
   raise ValueError('unclosed')
  return json.loads(t) if t.startswith('"') else t
 return read(next(it))
def child(seq,name):return next(x for x in seq if isinstance(x,list) and x and x[0]==name)
def test_exported_cad_net_connectivity():
 data=sexp((H/'RoomGuard_Baseboard_DRAFT.net').read_text());nets=child(data,'nets')[1:];mapping={}
 for n in nets:
  name=child(n,'name')[1].lstrip('/');mapping[name]={(child(node,'ref')[1],child(node,'pin')[1]) for node in n if isinstance(node,list) and node and node[0]=='node'}
 assert ('J7','4') in mapping['ADC32']
 assert ('J9','1') in mapping['ADC8266']
 assert ('U3','6') in mapping['SMOKE_MCU'] and ('J7','9') in mapping['SMOKE_MCU'] and ('J10','8') in mapping['SMOKE_MCU']
 # Physical SN74LVC2G17 pins:1A1,2GND,3A2,4Y2,5VCC,6Y1.
 assert ('U3','2') in mapping['GND'] and ('U3','3') in mapping['FLAME_IN']
 assert ('U3','5') in mapping['ESP_3V3']
 assert ('U1','5') in mapping['SENSOR_3V3'] and ('U1','5') not in mapping['ESP_3V3']
 assert ('Q3','2') in mapping['BUZZ_MCU'] and ('Q3','3') in mapping['BUZZ_INPUT']
 assert ('U2','1') in mapping['MQ_BUF'] and ('U2','2') in mapping['MQ_BUF']
def test_adc_limits_and_mechanical_not_approved():
 max32=5.25*10100/(19800+10100);max8266=5.25*10100/(55440+10100)
 assert max32<1.78 and max8266<.82
 m=json.loads((H/'mechanical.json').read_text());assert m['pitch_mm']==2.54 and m['pins_per_side']==15
 assert m['esp32_row_center_mm'] is None and m['esp8266_row_center_mm'] is None
 assert m['status']=='DRAFT_NOT_FOR_FABRICATION'
 assert not list(H.rglob('*.gbr'))

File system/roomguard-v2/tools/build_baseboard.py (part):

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def cap(ref,value,a,b,g='power'):add(ref,value,{1:a,2:b},CFP,g)
add('J1','5V INPUT 1=+5V 2=GND',{1:'RAW_5V',2:'GND'},'TerminalBlock:TerminalBlock_bornier-2_P5.08mm','power','Regulated5V only; no12V')
add('F1','PTC hold1.1A / trip2.2A',{1:'RAW_5V',2:'FUSED_IN'},'Fuse:Fuse_1206_3216Metric','power','Verify peak current and thermal derating')
add('Q1','AO3401A reverse-polarity',{1:'RP_GATE',2:'FUSED_OUT',3:'FUSED_IN'},'Package_TO_SOT_SMD:SOT-23','power','Pin1G 2S 3D; verify exact part')
resistor('R1','100k','RP_GATE','GND','power')
add('SW1','POWER SWITCH',{1:'FUSED_OUT',2:'P5V'},C2,'power','External switch header; do not bridge with metal while powered')
cap('C1','100uF/10V','P5V','GND');cap('C2','10uF','P5V','GND');cap('C3','100nF','P5V','GND')
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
